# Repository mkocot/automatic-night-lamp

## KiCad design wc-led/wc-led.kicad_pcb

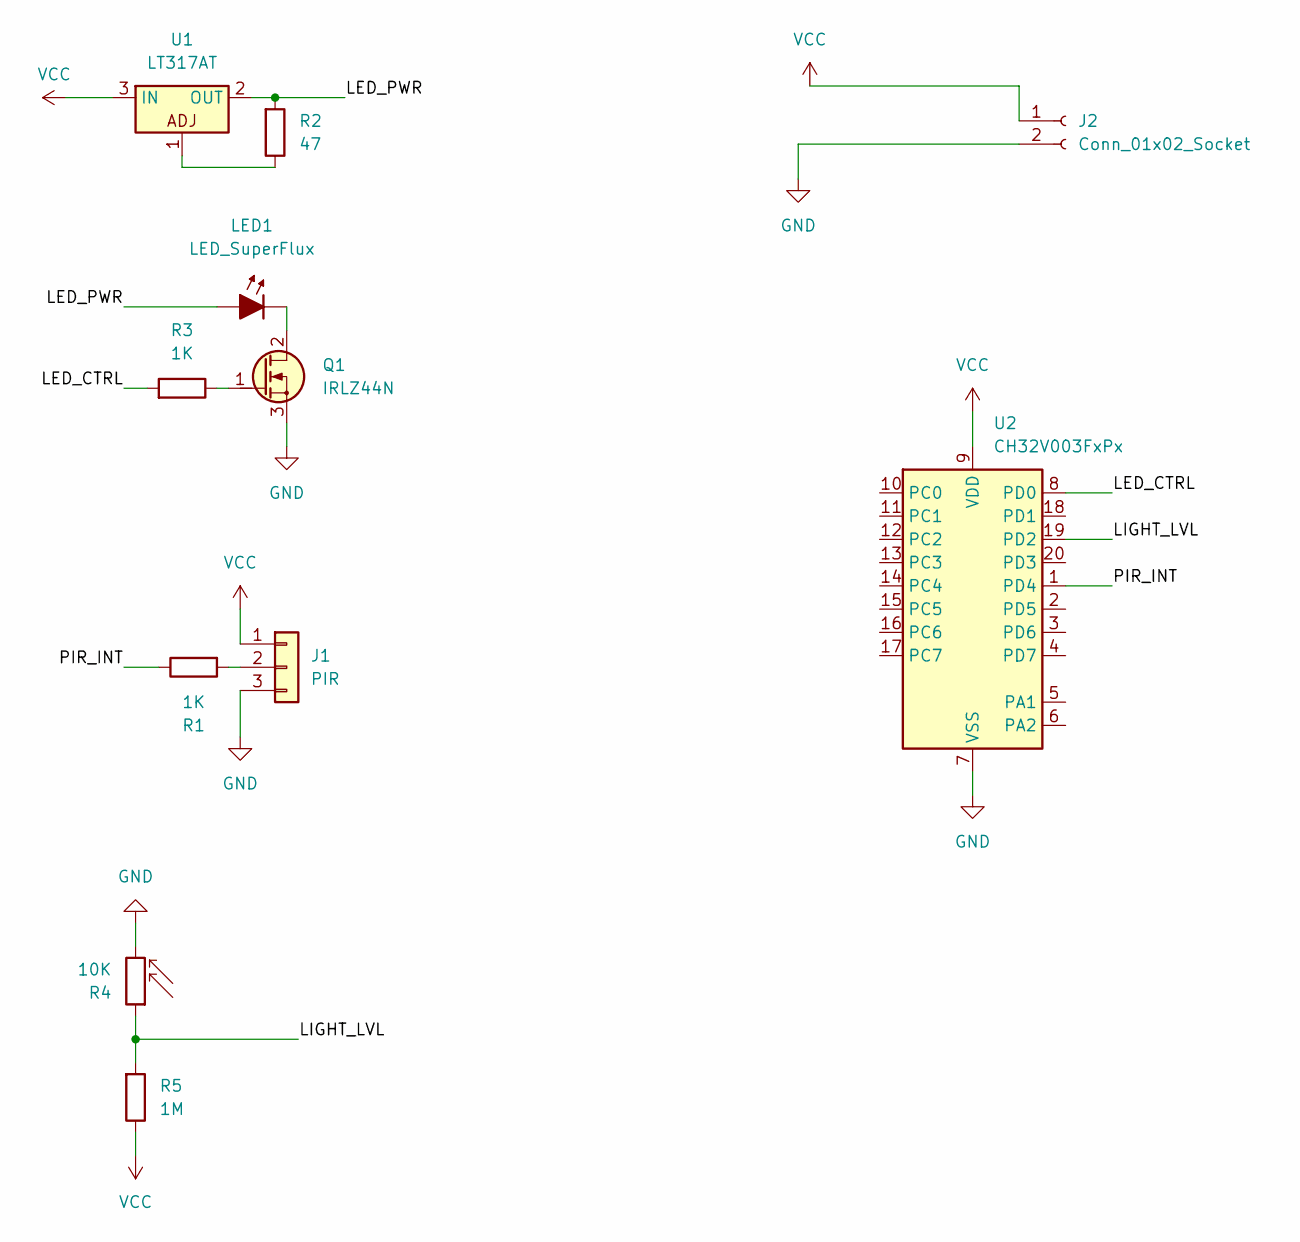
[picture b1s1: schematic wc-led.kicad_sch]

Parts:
J1: PIR
J2: Conn_01x02_Socket; JST_XH_B2B-XH-A_1x02_P2.50mm_Vertical
LED1: LED_SuperFlux
Q1: IRLZ44N; TO-220-3_Vertical_GDS
R1, R3: 1K; R_Axial_DIN0207_L6.3mm_D2.5mm_P2.54mm_Vertical
R2: 47; R_Axial_DIN0207_L6.3mm_D2.5mm_P2.54mm_Vertical
R4: 10K; R_LDR_D6.4mm_P3.4mm_Vertical
R5: 1M; R_Axial_DIN0207_L6.3mm_D2.5mm_P2.54mm_Vertical
U1: LT317AT; TO-220-3_Vertical
U2: CH32V003FxPx; DIP-20_W7.62mm

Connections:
/LED_CTRL: R3.1, U2.8 (PD0)
/LED_PWR: LED1.2 (A), R2.1, U1.2 (OUT)
/LIGHT_LVL: R4.1, R5.1, U2.19 (PD2)
/PIR_INT: R1.2, U2.1 (PD4)
GND: J1.3, J2.2, Q1.3 (S), R4.2, U2.7 (VSS)
unnamed: J1.2, R1.1
unnamed: LED1.1 (K), Q1.2 (D)
unnamed: Q1.1 (G), R3.2
unnamed: R2.2, U1.1
VCC: J1.1, J2.1, R5.2, U1.3 (IN), U2.9 (VDD)

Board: 2 copper layers, 10 parts (0 on the bottom side), 9 nets, no tracks yet.

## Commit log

2025-01-19 init
